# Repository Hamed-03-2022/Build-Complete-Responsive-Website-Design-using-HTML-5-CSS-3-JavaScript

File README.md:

# Build-Complete-Responsive-Website-Design-using-HTML-5-CSS-3-JavaScript
repo to practice from  https://www.youtube.com/watch?v=RHj5bdrfCr8&amp;list=PLajjpPyc2dmbt0KebBvT9VQV8y2R_IO7j&amp;index=3

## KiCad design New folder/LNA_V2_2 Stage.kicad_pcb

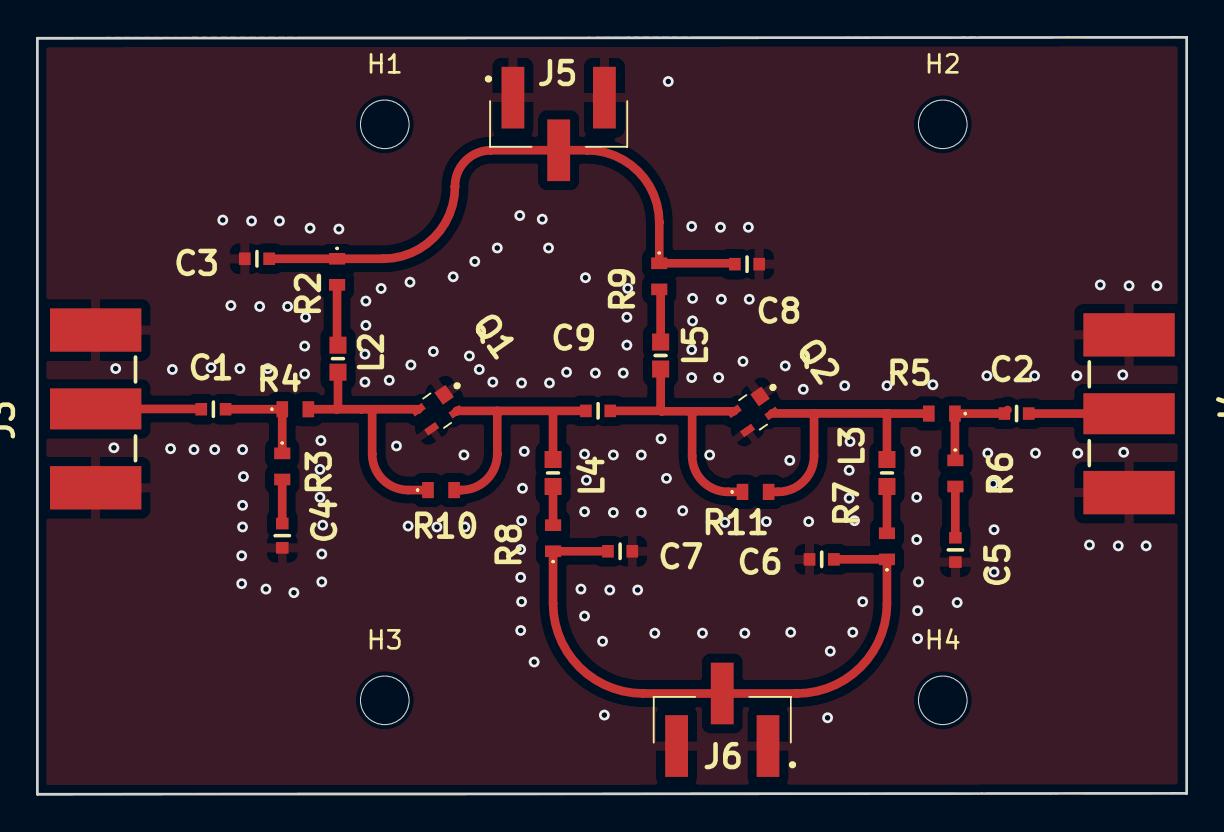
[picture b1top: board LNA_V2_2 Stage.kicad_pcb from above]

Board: 2 copper layers, 63.8 x 42.0 mm, 33 parts (0 on the bottom side), 17 nets.

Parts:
C1, C2, C3, C4, C5, C6, C7, C8, C9: C; GRM18x
H1, H2, H3, H4: MountingHole; MountingHole_2.7mm_M2.5_DIN965
J3, J4: 142-0701-801; 142-0701-851
J5, J6: TSM-103-01-T-SV; TSM10301TSV
L2, L3, L4, L5: L0603100GGSTR; INDC1608X71N
Q1, Q2: SKY65050-372LF; SKY65050372LF
R2, R3, R4, R5, R6, R7, R8, R9, R10, R11: ERA-3APB682V; ERA3AEB101V

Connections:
GND: C3.2, C4.1, C5.1, C6.2, C7.2, C8.2, J3.1, J3.3, J4.1, J4.3, J5.1, J5.3, J6.1, J6.3, Q1.1 (SOURCE_1), Q1.3 (SOURCE_2), Q2.1 (SOURCE_1), Q2.3 (SOURCE_2)
unnamed: C1.1, R3.1, R4.1
unnamed: C1.2, J3.2
unnamed: C2.1, R5.1, R6.1
unnamed: C2.2, J4.2
unnamed: C3.1, C8.1, J5.2, R2.1, R9.1
unnamed: C4.2, R3.2
unnamed: C5.2, R6.2
unnamed: C6.1, C7.1, J6.2, R7.1, R8.1
unnamed: L2.1, R2.2
unnamed: L3.1, R7.2
unnamed: L4.1, R8.2
unnamed: L5.1, R9.2
unnamed: C9.1, L4.2, Q1.2 (DRAIN), R10.2
unnamed: L2.2, Q1.4 (GATE), R4.2, R10.1
unnamed: L3.2, Q2.2 (DRAIN), R5.2, R11.2
unnamed: C9.2, L5.2, Q2.4 (GATE), R11.1
